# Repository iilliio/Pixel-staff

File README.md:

<h1>
Open Pixel Poi

</h1>

<h4>
  <a href="https://discord.gg/hErUF8A4">Store</a>
  ·
  <a href="./Firmware/MANUAL.md">User Guide</a>
  ·
  <a href="./Hardware/3D Printable Body/README.md">3D Models</a>
  ·
  <a href="./Hardware/Assembly/README.md">Assembly</a>
  ·
  <a href="./Software/README.md">Android App</a>
  ·
  <a href="https://mitchlol.github.io/#openpixelpoi">Firmware Tool</a>
  ·
  <a href="https://discord.gg/hErUF8A4">Discord</a>
</h4>

Open Pixel Poi  is an open source, 3D printable, LED pixel Poi, based around ESP32, WS2812B, and FFF/FDM manufacturing.
Designed to be simple, afforable, repairable, and customizable.
<div>

</div>

#### License
[Licensed  with GPLv3](https://www.gnu.org/licenses/gpl-3.0.en.html)
Suggested donation of 5$ per set of Poi built via [paypal](https://www.paypal.com/donate/?business=MTYSHEQVNBVNQ&amount=5&no_recurring=1&item_name=For+Creating+%26+Maintaing+Open+Pixel+Poi&currency_code=USD) or purchase PCBs from store link.

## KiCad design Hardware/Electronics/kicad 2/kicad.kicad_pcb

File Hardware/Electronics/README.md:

# Kicad project
This project was designed using Kicad, and is intended for jlcpcb smt assembly. If you would like to purchase a PCB, visit the store link in the [Readme](../../README.md)

If you want to build this without a custom PCB, you can build the [old version](https://github.com/Mitchlol/Open-Pixel-Poi/tree/v2.0.0/Hardware)
Just add an undocumented pull up resistor to the button.

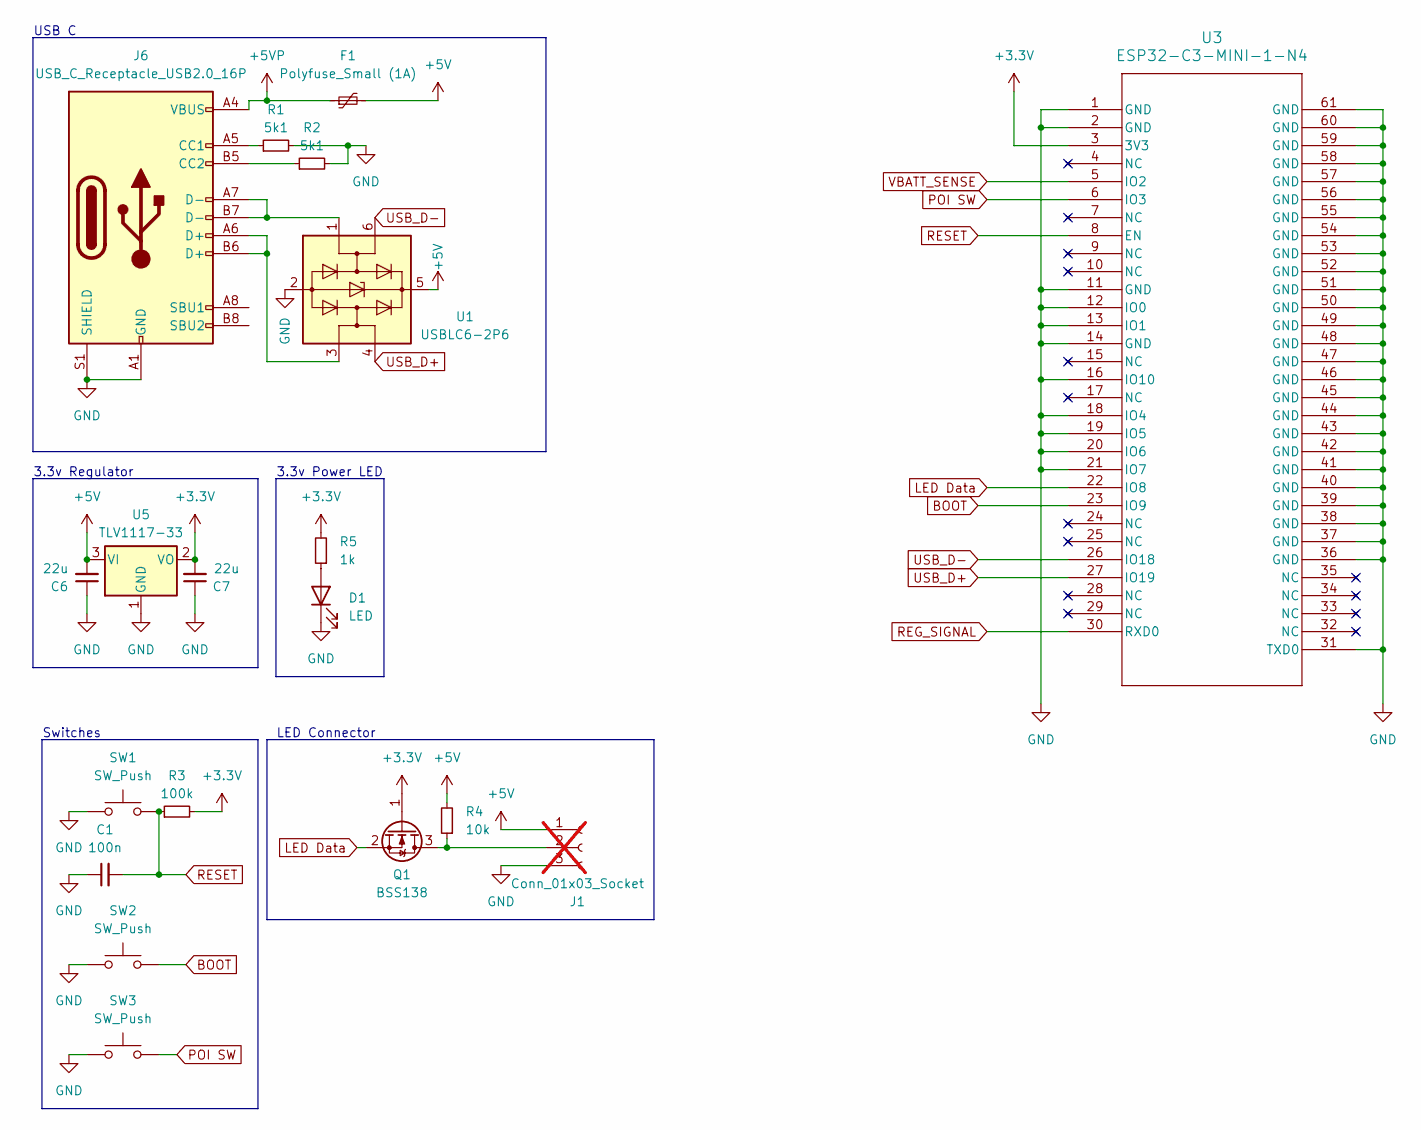
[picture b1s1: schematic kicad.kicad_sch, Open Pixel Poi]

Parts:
C1: 100n; C_0805_2012Metric; LCSC C5120075
C6, C7: 22u; C_0805_2012Metric; LCSC C86816
D1: LED; LED_0603_1608Metric; LCSC C965807
F1: Polyfuse_Small (1A); Fuse_1206_3216Metric; LCSC C720075
J1: Conn_01x03_Socket; JST_PH_B3B-PH-K_1x03_P2.00mm_Vertical; not fitted
J6: USB_C_Receptacle_USB2.0_16P; USB_C_Receptacle_HRO_TYPE-C-31-M-12; LCSC C2765186
Q1: BSS138; SOT-523; LCSC C5224244
R1, R2: 5k1; R_0603_1608Metric; LCSC C14677
R3: 100k; R_0603_1608Metric; LCSC C14675
R4: 10k; R_0603_1608Metric; LCSC C98220
R5: 1k; R_0603_1608Metric; LCSC C22548
SW1, SW2: SW_Push; SW_SPST_B3U-1000P; LCSC C231329
SW3: SW_Push; Panasonic_EVQPUL_EVQPUC; LCSC C79174
U1: USBLC6-2P6; SOT-666; LCSC C15999
U3: ESP32-C3-MINI-1-N4; ESP32-C3-MINI-1_EXP; LCSC C2934569
U5: TLV1117-33; SOT-223-3_TabPin2; LCSC C37359

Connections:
+3.3V: C7.2, Q1.1 (G), R3.2, R5.2, U3.3 (3V3), U5.2 (VO)
+5V: C6.2, F1.2, J1.1, R4.2, U1.5 (VBUS), U5.3 (VI)
+5VP: F1.1, J6.A4 (VBUS), J6.A9 (VBUS), J6.B4 (VBUS), J6.B9 (VBUS)
BOOT: SW2.2, U3.23 (IO9)
GND: C1.1, C6.1, C7.1, D1.1 (K), J1.3, J6.A1 (GND), J6.A12 (GND), J6.B1 (GND), J6.B12 (GND), J6.S1 (SHIELD), R1.2, R2.2, SW1.1, SW2.1, SW3.1, U1.2 (GND), U3.1 (GND), U3.2 (GND), U3.11 (GND), U3.12 (IO0), U3.13 (IO1), U3.14 (GND), U3.16 (IO10), U3.18 (IO4), U3.19 (IO5), U3.20 (IO6), U3.21 (IO7), U3.31 (TXD0), U3.36 (GND), U3.37 (GND), U3.38 (GND), U3.39 (GND), U3.40 (GND), U3.41 (GND), U3.42 (GND), U3.43 (GND), U3.44 (GND), U3.45 (GND), U3.46 (GND), U3.47 (GND), U3.48 (GND), U3.49 (GND), U3.50 (GND), U3.51 (GND), U3.52 (GND), U3.53 (GND), U3.54 (GND), U3.55 (GND), U3.56 (GND), U3.57 (GND), U3.58 (GND), U3.59 (GND), U3.60 (GND), U3.61 (GND), U5.1 (GND)
LED Data: Q1.2 (S), U3.22 (IO8)
unnamed: D1.2 (A), R5.1
unnamed: J1.2, Q1.3 (D), R4.1
unnamed: J6.A5 (CC1), R1.1
unnamed: J6.B5 (CC2), R2.1
unnamed: J6.A6 (D+), J6.B6 (D+), U1.3 (I/O2)
unnamed: J6.A7 (D-), J6.B7 (D-), U1.1 (I/O1)
POI SW: SW3.2, U3.6 (IO3)
REG_SIGNAL: U3.30 (RXD0)
RESET: C1.2, R3.1, SW1.2, U3.8 (EN)
USB_D+: U1.4 (I/O2), U3.27 (IO19)
USB_D-: U1.6 (I/O1), U3.26 (IO18)
VBATT_SENSE: U3.5 (IO2)

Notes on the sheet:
LED Connector
USB C
3.3v Regulator
3.3v Power LED
Switches

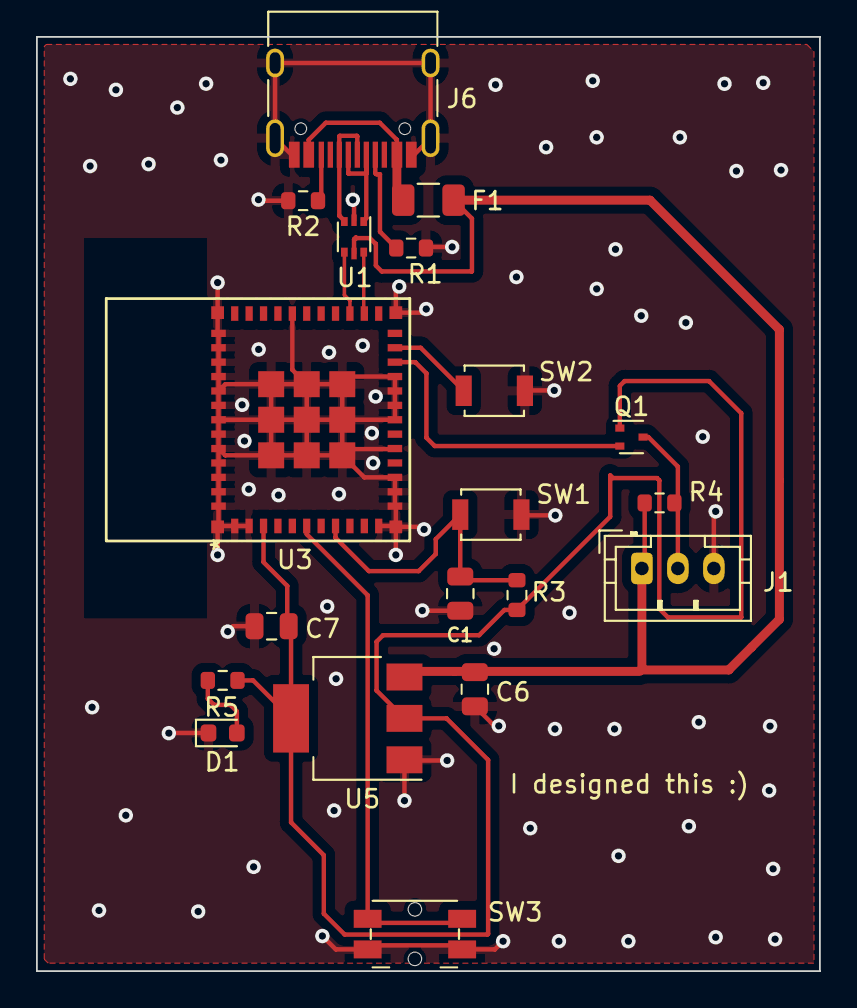
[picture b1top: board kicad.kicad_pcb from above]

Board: 2 copper layers, 43.5 x 51.9 mm, 19 parts (0 on the bottom side), 16 nets.

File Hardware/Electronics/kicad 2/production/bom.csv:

Designator,Footprint,Quantity,Value,LCSC Part #
C1,0805,1,100n,C5120075
"C6, C7",0805,2,22u,C86816
D1,0603,1,LED,C965807
F1,1206,1,Polyfuse_Small (1A),C720075
J6,USB_C_Receptacle_HRO_TYPE-C-31-M-12,1,USB_C_Receptacle_USB2.0_16P,C2765186
Q1,SOT-523,1,BSS138,C5224244
"R1, R2",0603,2,5k1,C14677
R3,0603,1,100k,C14675
R4,0603,1,10k,C98220
R5,0603,1,1k,C22548
"SW1, SW2",SW_SPST_B3U-1000P,2,SW_Push,C231329
SW3,Panasonic_EVQPUL_EVQPUC,1,SW_Push,C79174
U1,SOT-666,1,USBLC6-2P6,C15999
U3,ESP32-C3-MINI-1_EXP,1,ESP32-C3-MINI-1-N4,C2934569
U5,SOT-223-3_TabPin2,1,TLV1117-33,C37359

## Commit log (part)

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2023-05-11 add Firmware/led_remixer_firmware
2023-05-11 rename vars
2023-05-13 fix some buffer and data type issues; rename to open_pixel_poi
2023-05-13 rename to open_pixel_poi
2023-05-13 rename folder to open_pixel_poi_firmware
2023-05-13 rename from remixer to open pixel poi
2023-05-13 Add cosine pattern
2023-05-20 It can megaman kinda
2023-05-23 Gross but usable for now
2023-05-23 Did a bunch of stuff
2023-05-30 Migrate to v2 pinout, add sleep, voltage, brightness, and speed controls via button
2023-05-30 Add 3d model
2023-05-30 Update OpenPixelPoiAllParts.3mf
    Fixed battery sheath missing slots
2023-05-31 Realtime rendering, Better Speed control, tweak battery display, add switch info
2023-06-07 Connect to multiple Poi, Multiple file formats, Flip & Mirror Images
2023-06-09 Switch to flutter blue plus, fix reconnections
2023-06-09 Fix connection state indicator disconnects
2023-06-10 Add pattern selection
2023-06-10 Set pattern slot, better speed adjustment
2023-06-10 Add wiring diagram
2023-06-10 Readme updates
2023-06-22 Firmware updates
    Add pattern cycle mode with ble command, voltage display mode, low battery warnings, remove loop delay, prevent lockup on multipart ble timeout, improve shutdown, refactor button code, increase filte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
2023-06-23 App updates Block ui while uploading patterns Upload to each poi sequentially Cache images in memory Update default patterns Clean up db code a lil Add support for demo mode Change sliders into butto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
2023-07-01 Fix framerate aliasing issues
2023-07-02 Only send patterns to connected poi, timeout when confused about connection state
2023-09-19 Some app ui updates that have been sitting on my machine for months hopefully they work
2024-08-29 test board save state
    designed a breakout board, saving state so i can reference back to it if i ever need to, as i have a stack of them sitting around.
2024-11-24 Start on new PCB
2025-03-05 Hardware Updates
2025-03-23 Hardware 2.2.1
2025-03-23 Better low voltage handling
2025-03-25 Migrate mobile app to 2025 packages and ide
2025-03-26 Fix better ble transmissions and pattern updates
2025-03-26 Add pattern generators
2025-03-26 Add strobe pattern and other stuff
2025-03-26 try neopixelbus
2025-03-30 Add merge pattern creator and other tweaks
2025-03-30 Update fade to support list of colors
2025-03-30 tweak to the skip connection screen hack
2025-03-31 Create text
2025-03-31 Rename package
2025-03-31 Fix scan button
2025-04-01 Documentation updates
2025-04-01 Doc tweaks
2025-04-01 Update assembly guide
2025-04-03 Doc updates
2025-04-03 Disable auto connect, let lib request MTU for us, fix permissions
2025-04-03 Try to get a consistent splash screen
2025-04-04 Add multiple pattern banks
2025-04-04 Add apk
2025-04-04 rename file 1/2
2025-04-04 rename file 2/2
2025-04-04 Readme tweak
2025-04-05 PCB Tweaks
2025-04-10 Invert pattern output
2025-04-10 Few pcb tweaks
2025-04-10 Readme Update
2025-04-11 Add platform io version of firmware
2025-04-12 App updates, batch import, better tiling, better merging, display stats
2025-04-16 Add link to firmware flasher
2025-05-02 3D Files update
2025-05-02 Better readme links
2025-05-03 Fix firmware ble for web support
2025-05-08 80px version
2025-05-09 default height 80 in app
2025-07-28 working button with 1A module
2025-11-08 battery voltage adjust pixel fix
2025-11-08 adding s3 support
